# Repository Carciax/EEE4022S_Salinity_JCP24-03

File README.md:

## The Design of a Salinity Sensor for Antarctic Research
**EEE4022S_Salinity_JCP24-03**
 
This project focused on the design of a salinity sensor for measuring the salinity of the sea water beneath the Antarctica ice caps which had a unique habitat and salinity range due to the ice caps expelling large amount of salt through brine channels into the ocean below. The project consisted of two PCB boards, a probe to be inserted through a drilled hole in the ice and a controller to calibrate, request and display measurements. The probe used a complex switching array to measure the average resistance between a pair of either gold or titanium electrodes using a voltage sweep, then it would calculate the waters conductivity, and finally its salinity.

**File Structure**
- EEE4022S 2024 FINAL REPORT CLRCAM007 Clark CF - Pead: The final project report
- CAD: 3D printing files for the pressure sensor waterproof
- Code: The embedded C project code running on the controller and probe boards and the RS485 protocol between them.
- GA Forms: forms required to submit to ECSA
- PCBs: The KiCAD design files for the controller, probe and gold electrode PCBs.
- Presentation: Contains the power point and helper files for the final presentation
- Prototype: The prototype salinity sensor that preceeded this project.
- Report Helper Documents: Documents used for data processing and store from the testing of the probe.
- Report: The LaTeX project file for generating the final report.

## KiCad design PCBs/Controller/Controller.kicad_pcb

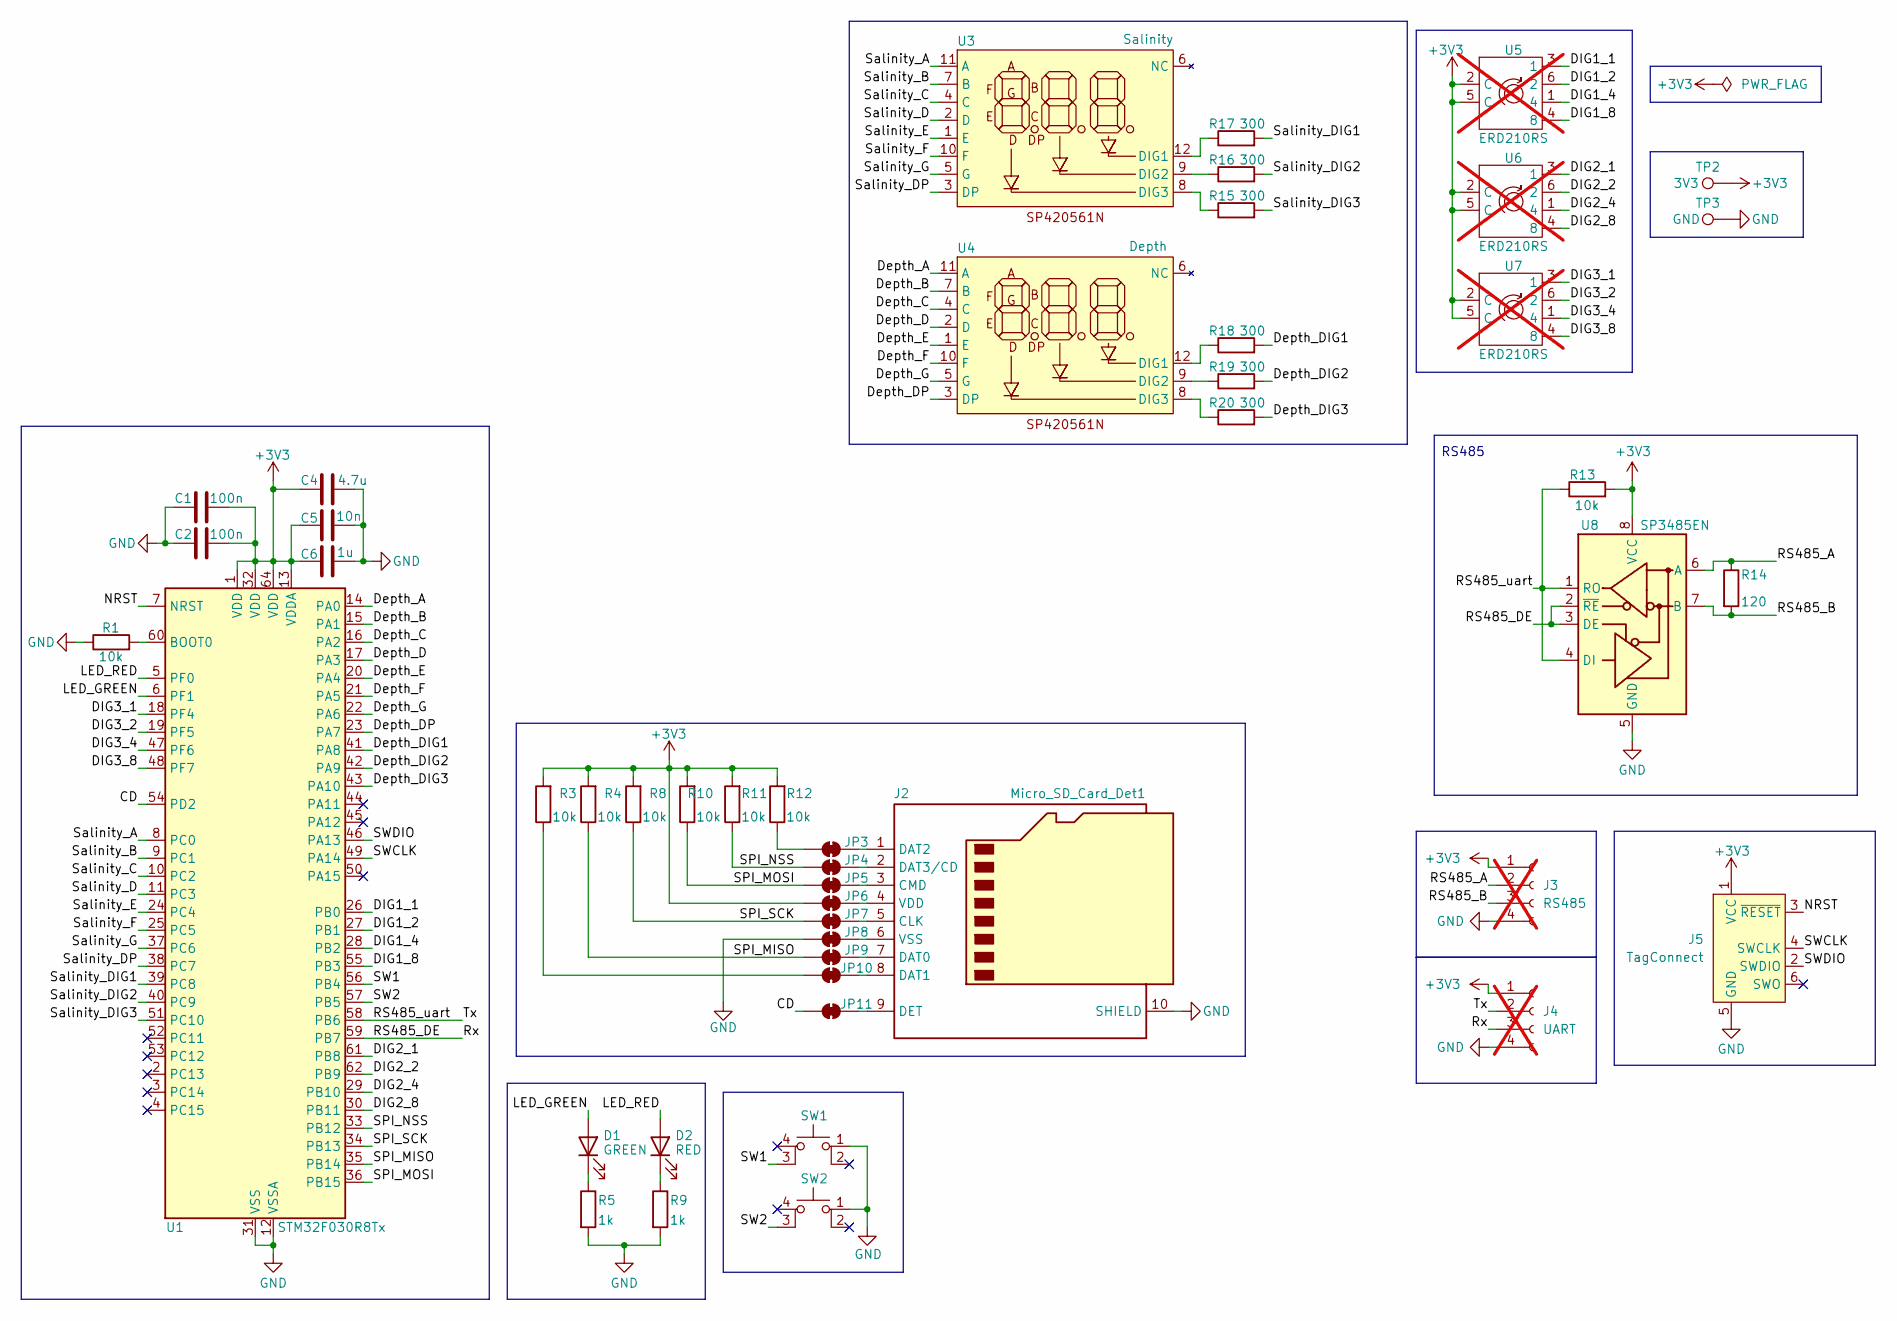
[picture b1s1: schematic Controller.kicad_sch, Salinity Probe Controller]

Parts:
C1, C2: 100n; C_0603_1608Metric; JLC Part no. C14663
C4: 4.7u; C_0603_1608Metric; JLC Part no. C69182
C5: 10n; C_0603_1608Metric; JLC Part no. C57112
C6: 1u; C_0603_1608Metric; JLC Part no. C15849
D1: GREEN; LED_0805_2012Metric; JLC Part no. C2297
D2: RED; LED_0603_1608Metric; JLC Part no. C2286
J2: Micro_SD_Card_Det1; microSDcard; JLC Part no. C393941
J3: RS485; PinHeader_1x04_P2.54mm_Vertical; not fitted
J4: UART; PinHeader_1x04_P2.54mm_Vertical; not fitted
J5: TagConnect; Tag-Connect_TC2030-IDC-NL_2x03_P1.27mm_Vertical
JP3, JP4, JP5, JP6, JP7, JP8, JP9, JP10, JP11: SolderJumper_2_Bridged; SolderJumper-2_P1.3mm_Bridged_Pad1.0x1.5mm
R1, R3, R4, R8, R10, R11, R12, R13: 10k; R_0603_1608Metric; JLC Part no. C25804
R5, R9: 1k; R_0603_1608Metric; JLC Part no. C21190
R14: 120; R_0603_1608Metric; JLC Part no. C22787
R15, R16, R17, R18, R19, R20: 300; R_1206_3216Metric; JLC Part no. C17887
SW1, SW2: Switch; Push_Button_SPDT; JLC Part no. C318884
TP2: 3V3; TestPoint_THTPad_2.0x2.0mm_Drill1.0mm
TP3: GND; TestPoint_THTPad_2.0x2.0mm_Drill1.0mm
U1: STM32F030R8Tx; LQFP-64_10x10mm_P0.5mm; JLC Part no. C39105
U3: Salinity; SP20561; JLC Part no. C98928
U4: Depth; SP20561; JLC Part no. C98928
U5, U6, U7: ERD210RS; ERD2xxxS; not fitted
U8: SP3485EN; SOIC-8_3.9x4.9mm_P1.27mm; JLC Part no. C8963

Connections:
+3V3: C1.2, C2.2, C4.1, C5.2, C6.2, J3.1, J4.1, J5.1 (VCC), JP6.1 (A), R3.2, R4.2, R8.2, R10.2, R11.2, R12.2, R13.2, TP2.1, U1.1 (VDD), U1.13 (VDDA), U1.32 (VDD), U1.64 (VDD), U5.2 (C), U5.5 (C), U6.2 (C), U6.5 (C), U7.2 (C), U7.5 (C), U8.8 (VCC)
/CD: JP11.1 (A), U1.54 (PD2)
/DIG1_1: U1.26 (PB0), U5.3 (1)
/DIG1_2: U1.27 (PB1), U5.6 (2)
/DIG1_4: U1.28 (PB2), U5.1 (4)
/DIG1_8: U1.55 (PB3), U5.4 (8)
/DIG2_1: U1.61 (PB8), U6.3 (1)
/DIG2_2: U1.62 (PB9), U6.6 (2)
/DIG2_4: U1.29 (PB10), U6.1 (4)
/DIG2_8: U1.30 (PB11), U6.4 (8)
/DIG3_1: U1.18 (PF4), U7.3 (1)
/DIG3_2: U1.19 (PF5), U7.6 (2)
/DIG3_4: U1.47 (PF6), U7.1 (4)
/DIG3_8: U1.48 (PF7), U7.4 (8)
/Depth_A: U1.14 (PA0), U4.11 (A)
/Depth_B: U1.15 (PA1), U4.7 (B)
/Depth_C: U1.16 (PA2), U4.4 (C)
/Depth_D: U1.17 (PA3), U4.2 (D)
/Depth_DIG1: R18.2, U1.41 (PA8)
/Depth_DIG2: R19.2, U1.42 (PA9)
/Depth_DIG3: R20.2, U1.43 (PA10)
/Depth_DP: U1.23 (PA7), U4.3 (DP)
/Depth_E: U1.20 (PA4), U4.1 (E)
/Depth_F: U1.21 (PA5), U4.10 (F)
/Depth_G: U1.22 (PA6), U4.5 (G)
/LED_GREEN: D1.2 (A), U1.6 (PF1)
/LED_RED: D2.2 (A), U1.5 (PF0)
/NRST: J5.3 (~RESET), U1.7 (NRST)
/RS485_A: J3.2, R14.1, U8.6 (A)
/RS485_B: J3.3, R14.2, U8.7 (B)
/RS485_DE: J4.3, U1.59 (PB7), U8.2 (~RE), U8.3 (DE)
/RS485_uart: J4.2, R13.1, U1.58 (PB6), U8.1 (RO), U8.4 (DI)
/SPI_MISO: JP9.1 (A), R4.1, U1.35 (PB14)
/SPI_MOSI: JP5.1 (A), R10.1, U1.36 (PB15)
/SPI_NSS: JP4.1 (A), R11.1, U1.33 (PB12)
/SPI_SCK: JP7.1 (A), R8.1, U1.34 (PB13)
/SW1: SW1.3 (K), U1.56 (PB4)
/SW2: SW2.3 (K), U1.57 (PB5)
/SWCLK: J5.4 (SWCLK), U1.49 (PA14)
/SWDIO: J5.2 (SWDIO), U1.46 (PA13)
/Salinity_A: U1.8 (PC0), U3.11 (A)
/Salinity_B: U1.9 (PC1), U3.7 (B)
/Salinity_C: U1.10 (PC2), U3.4 (C)
/Salinity_D: U1.11 (PC3), U3.2 (D)
/Salinity_DIG1: R17.2, U1.39 (PC8)
/Salinity_DIG2: R16.2, U1.40 (PC9)
/Salinity_DIG3: R15.2, U1.51 (PC10)
/Salinity_DP: U1.38 (PC7), U3.3 (DP)
/Salinity_E: U1.24 (PC4), U3.1 (E)
/Salinity_F: U1.25 (PC5), U3.10 (F)
/Salinity_G: U1.37 (PC6), U3.5 (G)
GND: C1.1, C2.1, C4.2, C5.1, C6.1, J2.10 (SHIELD), J3.4, J4.4, J5.5 (GND), JP8.1 (A), R1.1, R5.2, R9.2, SW1.1, SW2.1, TP3.1, U1.12 (VSSA), U1.31 (VSS), U1.63 (VSS), U8.5 (GND)
unnamed: D1.1 (K), R5.1
unnamed: D2.1 (K), R9.1
unnamed: J2.5 (CLK), JP7.2 (B)
unnamed: J2.3 (CMD), JP5.2 (B)
unnamed: J2.7 (DAT0), JP9.2 (B)
unnamed: J2.8 (DAT1), JP10.2 (B)
unnamed: J2.1 (DAT2), JP3.2 (B)
unnamed: J2.2 (DAT3/CD), JP4.2 (B)
unnamed: J2.9 (DET), JP11.2 (B)
unnamed: J2.4 (VDD), JP6.2 (B)
unnamed: J2.6 (VSS), JP8.2 (B)
unnamed: JP3.1 (A), R12.1
unnamed: JP10.1 (A), R3.1
unnamed: R1.2, U1.60 (BOOT0)
unnamed: R17.1, U3.12 (DIG1)
unnamed: R16.1, U3.9 (DIG2)
unnamed: R15.1, U3.8 (DIG3)
unnamed: R18.1, U4.12 (DIG1)
unnamed: R19.1, U4.9 (DIG2)
unnamed: R20.1, U4.8 (DIG3)

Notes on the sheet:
RS485

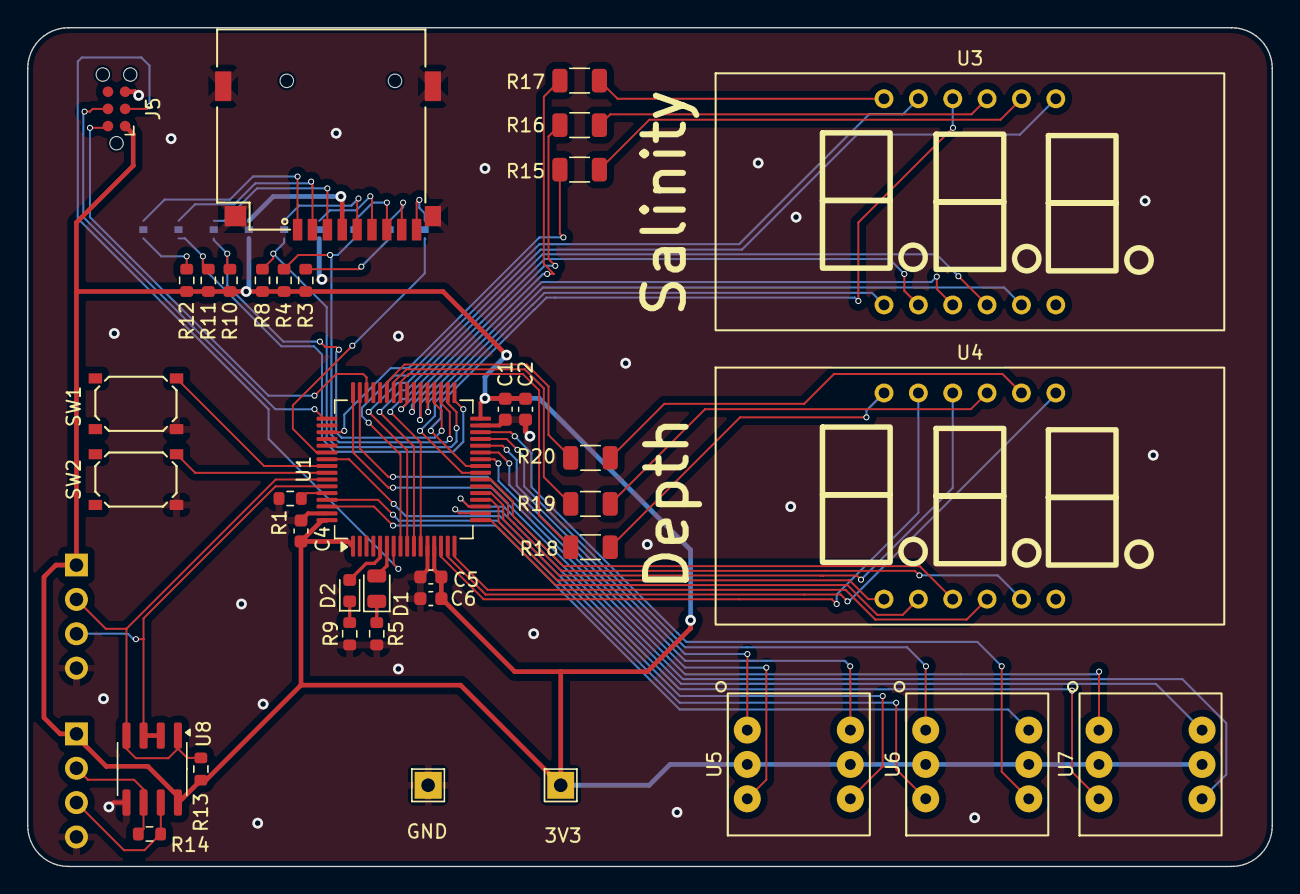
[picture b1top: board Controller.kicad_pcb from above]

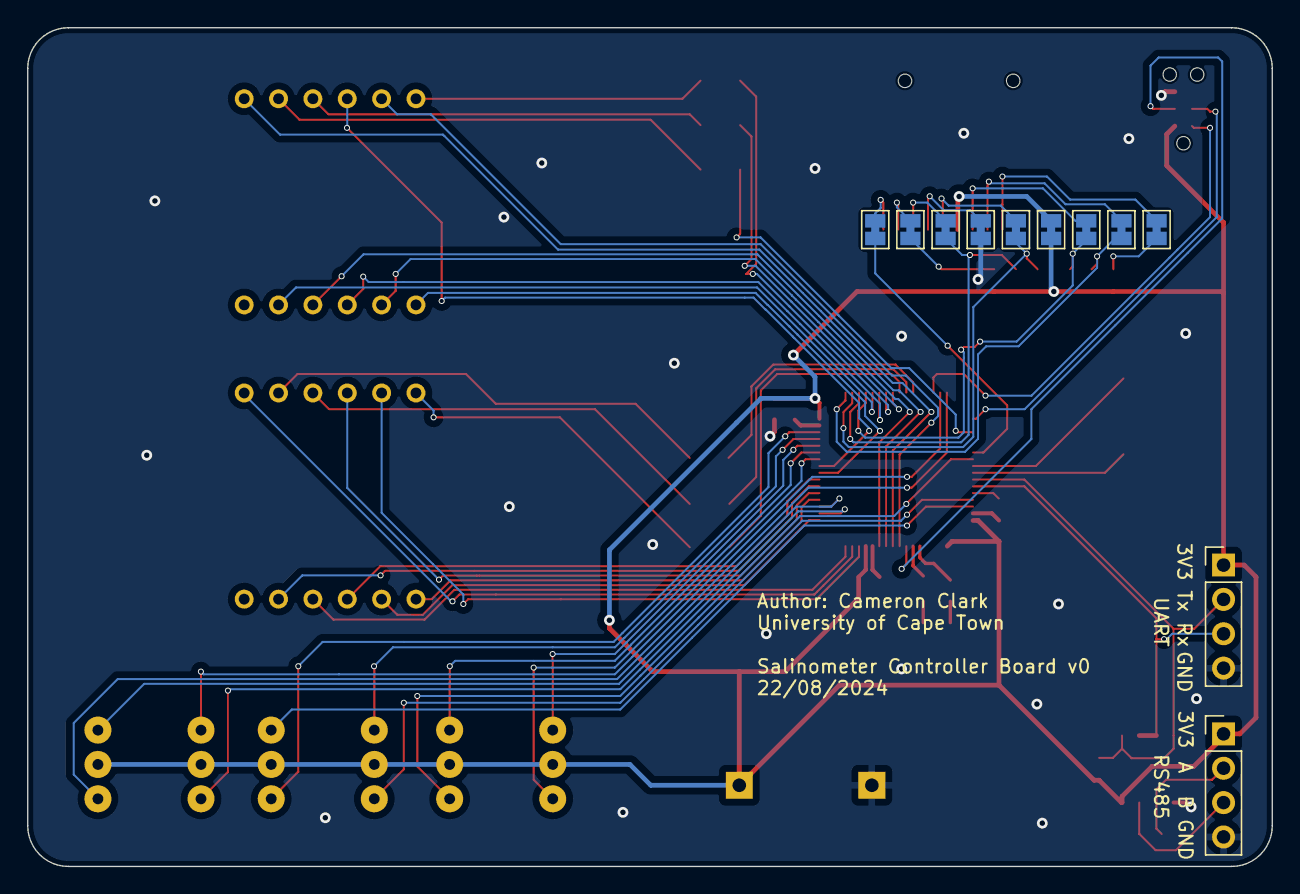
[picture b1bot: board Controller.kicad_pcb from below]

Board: 2 copper layers, 92.0 x 62.0 mm, 48 parts (11 on the bottom side), 72 nets.

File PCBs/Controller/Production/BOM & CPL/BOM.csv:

"Reference";"Value";"Datasheet";"Footprint";"Qty";"JLC Part no.";"Extended";"Cost"
"C1";"100n";"~";"Capacitor_SMD:C_0603_1608Metric";"1";"C14663";"False";"0,0021"
"C2";"100n";"~";"Capacitor_SMD:C_0603_1608Metric";"1";"C14663";"False";"0,0021"
"C4";"4.7u";"~";"Capacitor_SMD:C_0603_1608Metric";"1";"C69182";"False";"0,0055"
"C5";"10n";"~";"Capacitor_SMD:C_0603_1608Metric";"1";"C57112";"False";"0,0023"
"C6";"1u";"~";"Capacitor_SMD:C_0603_1608Metric";"1";"C15849";"False";"0,0043"
"D1";"GREEN";"~";"LED_SMD:LED_0805_2012Metric";"1";"C2297";"False";"0,0095"
"D2";"RED";"~";"LED_SMD:LED_0603_1608Metric";"1";"C2286";"False";"0,0053"
"J2";"Micro_SD_Card_Det1";"https://datasheet.lcsc.com/lcsc/2110151630_XKB-Connectivity-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";"4022S:microSDcard";"1";"C393941";"True";"0,0443"
"J3";"RS485";"~";"Connector_PinHeader_2.54mm:PinHeader_1x04_P2.54mm_Vertical";"1";"";"";""
"J4";"UART";"~";"Connector_PinHeader_2.54mm:PinHeader_1x04_P2.54mm_Vertical";"1";"";"";""
"R1";"10k";"~";"Resistor_SMD:R_0603_1608Metric";"1";"C25804";"False";"0,0008"
"R3";"10k";"~";"Resistor_SMD:R_0603_1608Metric";"1";"C25804";"False";"0,0008"
"R4";"10k";"~";"Resistor_SMD:R_0603_1608Metric";"1";"C25804";"False";"0,0008"
"R5";"1k";"~";"Resistor_SMD:R_0603_1608Metric";"1";"C21190";"False";"0,0009"
"R8";"10k";"~";"Resistor_SMD:R_0603_1608Metric";"1";"C25804";"False";"0,0008"
"R9";"1k";"~";"Resistor_SMD:R_0603_1608Metric";"1";"C21190";"False";"0,0009"
"R10";"10k";"~";"Resistor_SMD:R_0603_1608Metric";"1";"C25804";"False";"0,0008"
"R11";"10k";"~";"Resistor_SMD:R_0603_1608Metric";"1";"C25804";"False";"0,0008"
"R12";"10k";"~";"Resistor_SMD:R_0603_1608Metric";"1";"C25804";"False";"0,0008"
"R13";"10k";"~";"Resistor_SMD:R_0603_1608Metric";"1";"C25804";"False";"0,0008"
"R14";"120";"~";"Resistor_SMD:R_0603_1608Metric";"1";"C22787";"False";"0,0010"
"R15";"300";"~";"Resistor_SMD:R_1206_3216Metric";"1";"C17887";"False";"0,0028"
"R16";"300";"~";"Resistor_SMD:R_1206_3216Metric";"1";"C17887";"False";"0,0028"
"R17";"300";"~";"Resistor_SMD:R_1206_3216Metric";"1";"C17887";"False";"0,0028"
"R18";"300";"~";"Resistor_SMD:R_1206_3216Metric";"1";"C17887";"False";"0,0028"
"R19";"300";"~";"Resistor_SMD:R_1206_3216Metric";"1";"C17887";"False";"0,0028"
"R20";"300";"~";"Resistor_SMD:R_1206_3216Metric";"1";"C17887";"False";"0,0028"
"SW1";"Switch";"http://www.apem.com/int/index.php?controller=attachment&id_a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";"4022S:Push_Button_SPDT";"1";"C318884";"False";"0,0143"
"SW2";"Switch";"http://www.apem.com/int/index.php?controller=attachment&id_a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";"4022S:Push_Button_SPDT";"1";"C318884";"False";"0,0143"
"TP2";"3V3";"~";"TestPoint:TestPoint_THTPad_2.0x2.0mm_Drill1.0mm";"1";"";"";""
"TP3";"GND";"~";"TestPoint:TestPoint_THTPad_2.0x2.0mm_Drill1.0mm";"1";"";"";""
"U1";"STM32F030R8Tx";"https://www.st.com/resource/en/datasheet/stm32f030r8.pdf";"Package_QFP:LQFP-64_10x10mm_P0.5mm";"1";"C39105";"True";"0,7545"
"U3";"Salinity";"";"4022S:SP20561";"1";"C98928";"True";"0,4110"
"U4";"Depth";"";"4022S:SP20561";"1";"C98928";"True";"0,4110"
"U5";"ERD210RS";"";"4022S:ERD2xxxS";"1";"";"";""
"U6";"ERD210RS";"";"4022S:ERD2xxxS";"1";"";"";""
"U7";"ERD210RS";"";"4022S:ERD2xxxS";"1";"";"";""
"U8";"SP3485EN";"http://www.icbase.com/pdf/SPX/SPX00480106.pdf";"Package_SO:SOIC-8_3.9x4.9mm_P1.27mm";"1";"C8963";"False";"0,3076"

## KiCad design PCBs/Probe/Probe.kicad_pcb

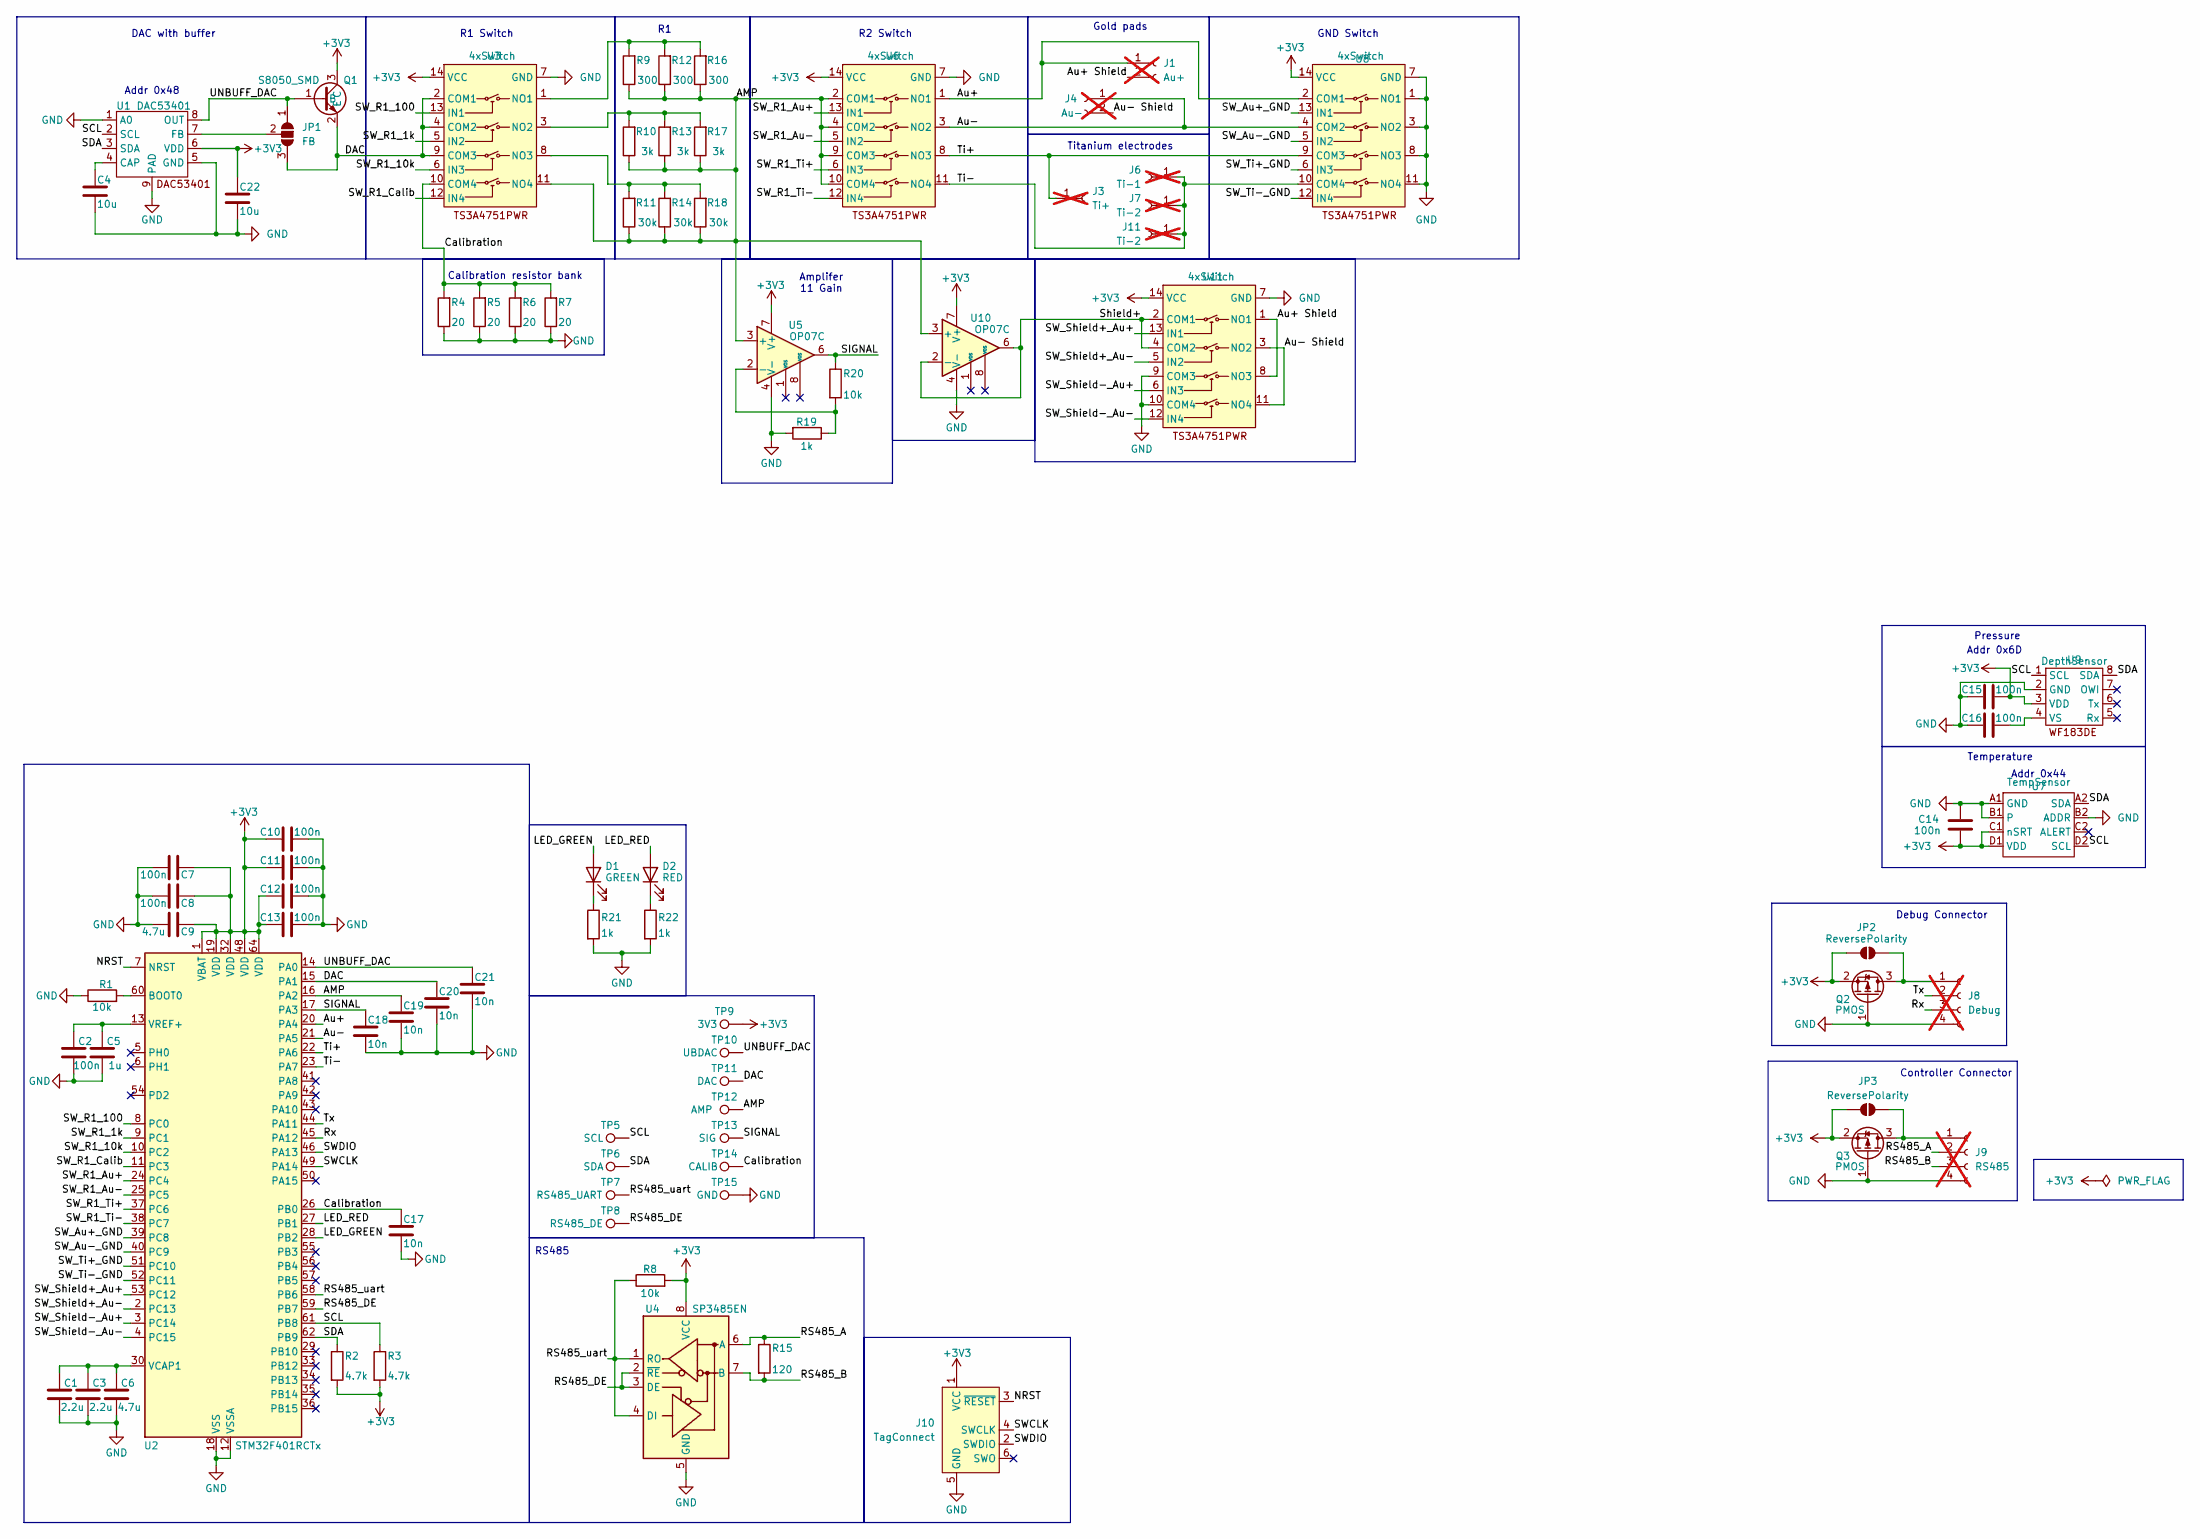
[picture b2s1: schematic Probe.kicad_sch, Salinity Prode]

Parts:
C1, C3: 2.2u; C_0603_1608Metric; JLC Part no. C23630
C2, C7, C8, C10, C11, C12, C13, C14, C15, C16: 100n; C_0603_1608Metric; JLC Part no. C14663
C4, C22: 10u; C_0603_1608Metric; JLC Part no. C19702
C5: 1u; C_0603_1608Metric; JLC Part no. C15849
C6, C9: 4.7u; C_0603_1608Metric; JLC Part no. C69182
C17, C18, C19, C20, C21: 10n; C_0402_1005Metric; JLC Part no. C15195
D1: GREEN; LED_0805_2012Metric; JLC Part no. C2297
D2: RED; LED_0603_1608Metric; JLC Part no. C2286
J1: Au+; Au_Electrode; not fitted
J3: Ti+; PinHeader_1x01_P2.54mm_Vertical; not fitted
J4: Au-; Au_Electrode; not fitted
J6: Ti-1; PinHeader_1x01_P2.54mm_Vertical; not fitted
J7, J11: Ti-2; PinHeader_1x01_P2.54mm_Vertical; not fitted
J8: Debug; PinSocket_1x04_P2.54mm_Vertical; not fitted
J9: RS485; PinSocket_1x04_P2.54mm_Vertical; not fitted
J10: TagConnect; Tag-Connect_TC2030-IDC-NL_2x03_P1.27mm_Vertical
JP1: FB; SolderJumper-3_P2.0mm_Open_TrianglePad1.0x1.5mm
JP2, JP3: ReversePolarity; SolderJumper-2_P1.3mm_Open_TrianglePad1.0x1.5mm
Q1: S8050_SMD; SOT-23-3; JLC Part no. C2146
Q2, Q3: PMOS; SOT-23; JLC Part no. C15127
R1, R8: 10k; R_0603_1608Metric; JLC Part no. C25804
R2, R3: 4.7k; R_0603_1608Metric; JLC Part no. C23162
R4, R5, R6, R7: 20; R_0603_1608Metric; JLC Part no. C22950
R9, R12, R16: 300; R_0603_1608Metric; JLC Part no. C23025
R10, R13, R17: 3k; R_0603_1608Metric; JLC Part no. C4211
R11, R14, R18: 30k; R_0603_1608Metric; JLC Part no. C22984
R15: 120; R_0603_1608Metric; JLC Part no. C22787
R19: 1k; R_1206_3216Metric; JLC Part no. C4410
R20: 10k; R_1206_3216Metric; JLC Part no. C17902
R21, R22: 1k; R_0603_1608Metric; JLC Part no. C21190
TP5: SCL; TestPoint_THTPad_2.0x2.0mm_Drill1.0mm
TP6: SDA; TestPoint_THTPad_2.0x2.0mm_Drill1.0mm
TP7: RS485_UART; TestPoint_THTPad_2.0x2.0mm_Drill1.0mm
TP8: RS485_DE; TestPoint_THTPad_2.0x2.0mm_Drill1.0mm
TP9: 3V3; TestPoint_THTPad_2.0x2.0mm_Drill1.0mm
TP10: UBDAC; TestPoint_THTPad_2.0x2.0mm_Drill1.0mm
TP11: DAC; TestPoint_THTPad_2.0x2.0mm_Drill1.0mm
TP12: AMP; TestPoint_THTPad_2.0x2.0mm_Drill1.0mm
TP13: SIG; TestPoint_THTPad_2.0x2.0mm_Drill1.0mm
TP14: CALIB; TestPoint_THTPad_2.0x2.0mm_Drill1.0mm
TP15: GND; TestPoint_THTPad_2.0x2.0mm_Drill1.0mm
U1: DAC53401; WSON-8-1EP_2x2mm_P0.5mm_EP0.9x1.6mm; JLC Part no. C2861165
U2: STM32F401RCTx; LQFP-64_10x10mm_P0.5mm; JLC Part no. C1339473
U3, U6, U8, U11: 4xSwitch; TSSOP-14_4.4x5mm_P0.65mm; JLC Part no. C128399
U4: SP3485EN; SOIC-8_3.9x4.9mm_P1.27mm; JLC Part no. C8963
U5, U10: OP07C; SOIC-8_3.9x4.9mm_P1.27mm; JLC Part no. C7433
U7: TempSensor; WLCSP-8_1.551x2.284mm_P0.5mm; JLC Part no. C2758003
U9: DepthSensor; WF183DE; JLC Part no. C20415992

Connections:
+3V3: C7.1, C8.1, C9.1, C10.1, C11.1, C12.1, C13.1, C14.2, C15.2, C22.1, J10.1 (VCC), JP2.1 (A), JP3.1 (A), Q1.3 (C), Q2.2 (S), Q3.2 (S), R2.2, R3.2, R8.2, TP9.1, U1.6 (VDD), U2.1 (VBAT), U2.19 (VDD), U2.32 (VDD), U2.48 (VDD), U2.64 (VDD), U3.14 (VCC), U4.8 (VCC), U5.7 (V+), U6.14 (VCC), U7.C1 (nSRT), U7.D1 (VDD), U8.14 (VCC), U9.3 (VDD), U10.7 (V+), U11.14 (VCC)
/AMP: C19.1, R9.1, R10.1, R11.1, R12.1, R13.1, R14.1, R16.1, R17.1, R18.1, TP12.1, U2.16 (PA2), U3.11 (NO4), U5.3 (+), U6.2 (COM1), U6.4 (COM2), U6.9 (COM3), U6.10 (COM4), U10.3 (+)
/Au+: J1.1, U2.20 (PA4), U6.1 (NO1), U8.2 (COM1)
/Au+ Shield: J1.2, U11.1 (NO1), U11.8 (NO3)
/Au-: J4.1, U2.21 (PA5), U6.3 (NO2), U8.4 (COM2)
/Au- Shield: J4.2, U11.3 (NO2), U11.11 (NO4)
/Calibration: C17.1, R4.2, R5.2, R6.2, R7.2, TP14.1, U2.26 (PB0), U3.10 (COM4)
/DAC: C20.1, JP1.3 (B), Q1.2 (E), TP11.1, U2.15 (PA1), U3.2 (COM1), U3.4 (COM2), U3.9 (COM3)
/LED_GREEN: D1.2 (A), U2.28 (PB2)
/LED_RED: D2.2 (A), U2.27 (PB1)
/NRST: J10.3 (~RESET), U2.7 (NRST)
/RS485_A: J9.2, R15.1, U4.6 (A)
/RS485_B: J9.3, R15.2, U4.7 (B)
/RS485_DE: TP8.1, U2.59 (PB7), U4.2 (~RE), U4.3 (DE)
/RS485_uart: R8.1, TP7.1, U2.58 (PB6), U4.1 (RO), U4.4 (DI)
/Rx: J8.3, U2.45 (PA12)
/SCL: R3.1, TP5.1, U1.2 (SCL), U2.61 (PB8), U7.D2 (SCL), U9.1 (SCL)
/SDA: R2.1, TP6.1, U1.3 (SDA), U2.62 (PB9), U7.A2 (SDA), U9.8 (SDA)
/SIGNAL: C18.1, R20.1, TP13.1, U2.17 (PA3), U5.6
/SWCLK: J10.4 (SWCLK), U2.49 (PA14)
/SWDIO: J10.2 (SWDIO), U2.46 (PA13)
/SW_Au+_GND: U2.39 (PC8), U8.13 (IN1)
/SW_Au-_GND: U2.40 (PC9), U8.5 (IN2)
/SW_R1_1k: U2.9 (PC1), U3.5 (IN2)
/SW_R1_10k: U2.10 (PC2), U3.6 (IN3)
/SW_R1_100: U2.8 (PC0), U3.13 (IN1)
/SW_R1_Au+: U2.24 (PC4), U6.13 (IN1)
/SW_R1_Au-: U2.25 (PC5), U6.5 (IN2)
/SW_R1_Calib: U2.11 (PC3), U3.12 (IN4)
/SW_R1_Ti+: U2.37 (PC6), U6.6 (IN3)
/SW_R1_Ti-: U2.38 (PC7), U6.12 (IN4)
/SW_Shield+_Au+: U2.53 (PC12), U11.13 (IN1)
/SW_Shield+_Au-: U2.2 (PC13), U11.5 (IN2)
/SW_Shield-_Au+: U2.3 (PC14), U11.6 (IN3)
/SW_Shield-_Au-: U2.4 (PC15), U11.12 (IN4)
/SW_Ti+_GND: U2.51 (PC10), U8.6 (IN3)
/SW_Ti-_GND: U2.52 (PC11), U8.12 (IN4)
/Shield+: U10.2 (-), U10.6, U11.2 (COM1), U11.4 (COM2)
/Ti+: J3.1, U2.22 (PA6), U6.8 (NO3), U8.9 (COM3)
/Ti-: J6.1, J7.1, J11.1, U2.23 (PA7), U6.11 (NO4), U8.10 (COM4)
/Tx: J8.2, U2.44 (PA11)
/UNBUFF_DAC: C21.1, JP1.1 (A), Q1.1 (B), TP10.1, U1.8 (OUT), U2.14 (PA0)
GND: C1.1, C2.1, C3.1, C4.2, C5.1, C6.1, C7.2, C8.2, C9.2, C10.2, C11.2, C12.2, C13.2, C14.1, C15.1, C16.1, C17.2, C18.2, C19.2, C20.2, C21.2, C22.2, J8.4, J9.4, J10.5 (GND), Q2.1 (G), Q3.1 (G), R1.1, R4.1, R5.1, R6.1, R7.1, R19.2, R21.2, R22.2, TP15.1, U1.1 (A0), U1.5 (GND), U1.9 (PAD), U2.12 (VSSA), U2.18 (VSS), U2.31 (VSS), U2.47 (VSS), U2.63 (VSS), U3.7 (GND), U4.5 (GND), U5.4 (V-), U6.7 (GND), U7.A1 (GND), U7.B1, U7.B2 (ADDR), U8.1 (NO1), U8.3 (NO2), U8.7 (GND), U8.8 (NO3), U8.11 (NO4), U9.2 (GND), U10.4 (V-), U11.7 (GND), U11.9 (COM3), U11.10 (COM4)
unnamed: D1.1 (K), R21.1
unnamed: D2.1 (K), R22.1
unnamed: J8.1, JP2.2 (B), Q2.3 (D)
unnamed: J9.1, JP3.2 (B), Q3.3 (D)
unnamed: JP1.2 (C), U1.7 (FB)
unnamed: C4.1, U1.4 (CAP)
unnamed: R1.2, U2.60 (BOOT0)
unnamed: C1.2, C3.2, C6.2, U2.30 (VCAP1)
unnamed: C2.2, C5.2, U2.13 (VREF+)
unnamed: R9.2, R12.2, R16.2, U3.1 (NO1)
unnamed: R10.2, R13.2, R17.2, U3.3 (NO2)
unnamed: R11.2, R14.2, R18.2, U3.8 (NO3)
unnamed: R19.1, R20.2, U5.2 (-)
unnamed: C16.2, U9.4 (VS)

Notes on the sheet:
R1 Switch
Gold pads
GND Switch
Debug Connector
Pressure
Addr 0x48
RS485
DAC with buffer
Addr 0x44
Calibration resistor bank
Controller Connector
Titanium electrodes
R2 Switch
Amplifer 11 Gain
Addr 0x6D
Temperature

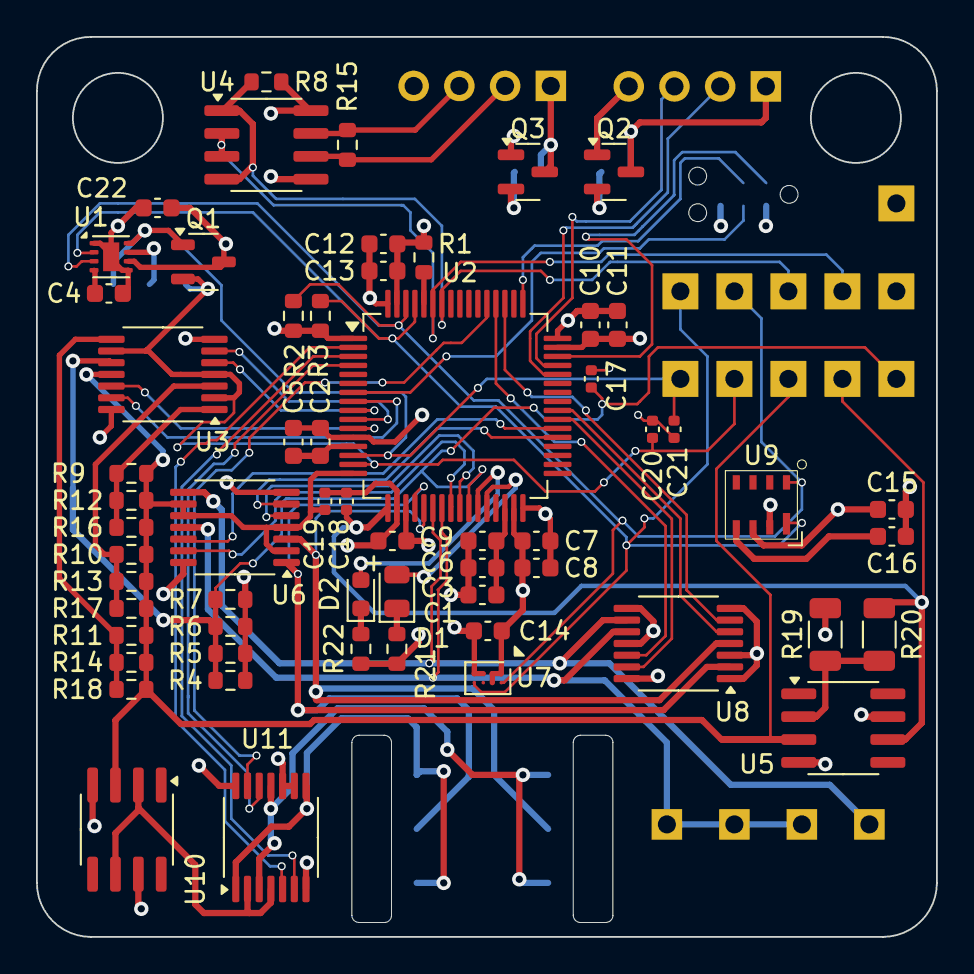
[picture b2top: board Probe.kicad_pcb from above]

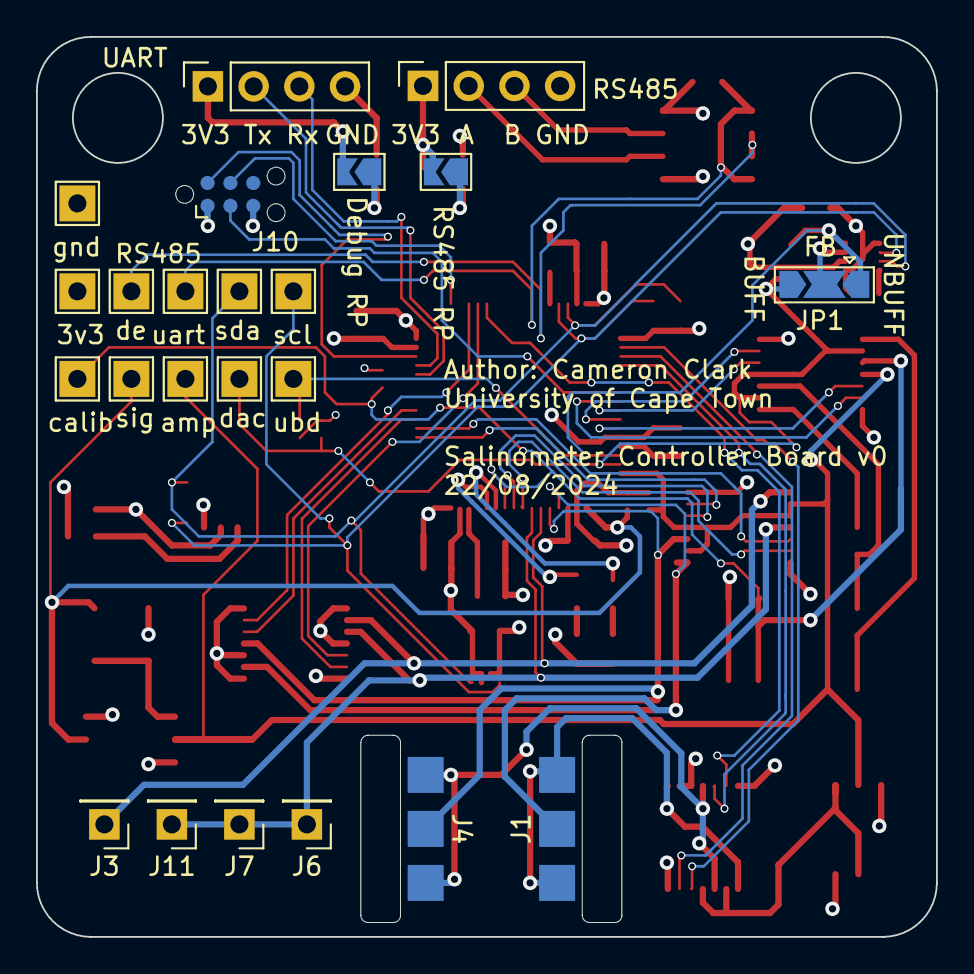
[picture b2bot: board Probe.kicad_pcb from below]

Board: 4 copper layers, 50.0 x 50.0 mm, 83 parts (23 on the bottom side), 57 nets.

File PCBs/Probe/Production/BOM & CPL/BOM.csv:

"Reference";"Value";"Datasheet";"Footprint";"Qty";"JLC Part no.";"Extended";"Cost"
"C1";"2.2u";"~";"Capacitor_SMD:C_0603_1608Metric";"1";"C23630";"False";"0,0055"
"C2";"100n";"~";"Capacitor_SMD:C_0603_1608Metric";"1";"C14663";"False";"0,0021"
"C3";"2.2u";"~";"Capacitor_SMD:C_0603_1608Metric";"1";"C23630";"False";"0,0055"
"C4";"10u";"~";"Capacitor_SMD:C_0603_1608Metric";"1";"C19702";"False";"0,0048"
"C5";"1u";"~";"Capacitor_SMD:C_0603_1608Metric";"1";"C15849";"False";"0,0043"
"C6";"4.7u";"~";"Capacitor_SMD:C_0603_1608Metric";"1";"C69182";"False";"0,0055"
"C7";"100n";"~";"Capacitor_SMD:C_0603_1608Metric";"1";"C14663";"False";"0,0021"
"C8";"100n";"~";"Capacitor_SMD:C_0603_1608Metric";"1";"C14663";"False";"0,0021"
"C9";"4.7u";"~";"Capacitor_SMD:C_0603_1608Metric";"1";"C69182";"False";"0,0055"
"C10";"100n";"~";"Capacitor_SMD:C_0603_1608Metric";"1";"C14663";"False";"0,0021"
"C11";"100n";"~";"Capacitor_SMD:C_0603_1608Metric";"1";"C14663";"False";"0,0021"
"C12";"100n";"~";"Capacitor_SMD:C_0603_1608Metric";"1";"C14663";"False";"0,0021"
"C13";"100n";"~";"Capacitor_SMD:C_0603_1608Metric";"1";"C14663";"False";"0,0021"
"C14";"100n";"~";"Capacitor_SMD:C_0603_1608Metric";"1";"C14663";"False";"0,0021"
"C15";"100n";"~";"Capacitor_SMD:C_0603_1608Metric";"1";"C14663";"False";"0,0021"
"C16";"100n";"~";"Capacitor_SMD:C_0603_1608Metric";"1";"C14663";"False";"0,0021"
"C17";"10n";"~";"Capacitor_SMD:C_0402_1005Metric";"1";"C15195";"False";"0,0012"
"C18";"10n";"~";"Capacitor_SMD:C_0402_1005Metric";"1";"C15195";"False";"0,0012"
"C19";"10n";"~";"Capacitor_SMD:C_0402_1005Metric";"1";"C15195";"False";"0,0012"
"C20";"10n";"~";"Capacitor_SMD:C_0402_1005Metric";"1";"C15195";"False";"0,0012"
"C21";"10n";"~";"Capacitor_SMD:C_0402_1005Metric";"1";"C15195";"False";"0,0012"
"C22";"10u";"~";"Capacitor_SMD:C_0603_1608Metric";"1";"C19702";"False";"0,0048"
"D1";"GREEN";"~";"LED_SMD:LED_0805_2012Metric";"1";"C2297";"False";"0,0095"
"D2";"RED";"~";"LED_SMD:LED_0603_1608Metric";"1";"C2286";"False";"0,0053"
"J1";"Au+";"~";"4022S:Au_Electrode";"1";"";"";""
"J3";"Ti+";"~";"Connector_PinHeader_2.54mm:PinHeader_1x01_P2.54mm_Vertical";"1";"";"";""
"J4";"Au-";"~";"4022S:Au_Electrode";"1";"";"";""
"J6";"Ti-1";"~";"Connector_PinHeader_2.54mm:PinHeader_1x01_P2.54mm_Vertical";"1";"";"";""
"J7";"Ti-2";"~";"Connector_PinHeader_2.54mm:PinHeader_1x01_P2.54mm_Vertical";"1";"";"";""
"J8";"Debug";"~";"Connector_PinSocket_2.54mm:PinSocket_1x04_P2.54mm_Vertical";"1";"";"";""
"J9";"RS485";"~";"Connector_PinSocket_2.54mm:PinSocket_1x04_P2.54mm_Vertical";"1";"";"";""
"J11";"Ti-2";"~";"Connector_PinHeader_2.54mm:PinHeader_1x01_P2.54mm_Vertical";"1";"";"";""
"Q1";"S8050_SMD";"";"Package_TO_SOT_SMD:SOT-23-3";"1";"C2146";"False";"0,0131"
"Q2";"PMOS";"http://www.aosmd.com/pdfs/datasheet/AO3401A.pdf";"Package_TO_SOT_SMD:SOT-23";"1";"C15127";"False";"0,0387"
"Q3";"PMOS";"http://www.aosmd.com/pdfs/datasheet/AO3401A.pdf";"Package_TO_SOT_SMD:SOT-23";"1";"C15127";"False";"0,0387"
"R1";"10k";"~";"Resistor_SMD:R_0603_1608Metric";"1";"C25804";"False";"0,0008"
"R2";"4.7k";"~";"Resistor_SMD:R_0603_1608Metric";"1";"C23162";"False";"0,0010"
"R3";"4.7k";"~";"Resistor_SMD:R_0603_1608Metric";"1";"C23162";"False";"0,0010"
"R4";"20";"~";"Resistor_SMD:R_0603_1608Metric";"1";"C22950";"False";"0,0009"
"R5";"20";"~";"Resistor_SMD:R_0603_1608Metric";"1";"C22950";"False";"0,0009"
"R6";"20";"~";"Resistor_SMD:R_0603_1608Metric";"1";"C22950";"False";"0,0009"
"R7";"20";"~";"Resistor_SMD:R_0603_1608Metric";"1";"C22950";"False";"0,0009"
"R8";"10k";"~";"Resistor_SMD:R_0603_1608Metric";"1";"C25804";"False";"0,0008"
"R9";"300";"~";"Resistor_SMD:R_0603_1608Metric";"1";"C23025";"False";"0,0010"
"R10";"3k";"~";"Resistor_SMD:R_0603_1608Metric";"1";"C4211";"False";"0,0009"
"R11";"30k";"~";"Resistor_SMD:R_0603_1608Metric";"1";"C22984";"False";"0,0009"
"R12";"300";"~";"Resistor_SMD:R_0603_1608Metric";"1";"C23025";"False";"0,0010"
"R13";"3k";"~";"Resistor_SMD:R_0603_1608Metric";"1";"C4211";"False";"0,0009"
"R14";"30k";"~";"Resistor_SMD:R_0603_1608Metric";"1";"C22984";"False";"0,0009"
"R15";"120";"~";"Resistor_SMD:R_0603_1608Metric";"1";"C22787";"False";"0,0010"
"R16";"300";"~";"Resistor_SMD:R_0603_1608Metric";"1";"C23025";"False";"0,0010"
"R17";"3k";"~";"Resistor_SMD:R_0603_1608Metric";"1";"C4211";"False";"0,0009"
"R18";"30k";"~";"Resistor_SMD:R_0603_1608Metric";"1";"C22984";"False";"0,0009"
"R19";"1k";"~";"Resistor_SMD:R_1206_3216Metric";"1";"C4410";"False";"0,0027"
"R20";"10k";"~";"Resistor_SMD:R_1206_3216Metric";"1";"C17902";"False";"0,0028"
"R21";"1k";"~";"Resistor_SMD:R_0603_1608Metric";"1";"C21190";"False";"0,0009"
"R22";"1k";"~";"Resistor_SMD:R_0603_1608Metric";"1";"C21190";"False";"0,0009"
"TP5";"SCL";"~";"TestPoint:TestPoint_THTPad_2.0x2.0mm_Drill1.0mm";"1";"";"";""
"TP6";"SDA";"~";"TestPoint:TestPoint_THTPad_2.0x2.0mm_Drill1.0mm";"1";"";"";""
"TP7";"RS485_UART";"~";"TestPoint:TestPoint_THTPad_2.0x2.0mm_Drill1.0mm";"1";"";"";""
"TP8";"RS485_DE";"~";"TestPoint:TestPoint_THTPad_2.0x2.0mm_Drill1.0mm";"1";"";"";""
"TP9";"3V3";"~";"TestPoint:TestPoint_THTPad_2.0x2.0mm_Drill1.0mm";"1";"";"";""
"TP10";"UBDAC";"~";"TestPoint:TestPoint_THTPad_2.0x2.0mm_Drill1.0mm";"1";"";"";""
"TP11";"DAC";"~";"TestPoint:TestPoint_THTPad_2.0x2.0mm_Drill1.0mm";"1";"";"";""
"TP12";"AMP";"~";"TestPoint:TestPoint_THTPad_2.0x2.0mm_Drill1.0mm";"1";"";"";""
"TP13";"SIG";"~";"TestPoint:TestPoint_THTPad_2.0x2.0mm_Drill1.0mm";"1";"";"";""
"TP14";"CALIB";"~";"TestPoint:TestPoint_THTPad_2.0x2.0mm_Drill1.0mm";"1";"";"";""
"TP15";"GND";"~";"TestPoint:TestPoint_THTPad_2.0x2.0mm_Drill1.0mm";"1";"";"";""
"U1";"DAC53401";"";"Package_SON:WSON-8-1EP_2x2mm_P0.5mm_EP0.9x1.6mm";"1";"C2861165";"True";"0,6660"
"U2";"STM32F401RCTx";"https://www.st.com/resource/en/datasheet/stm32f401rc.pdf";"Package_QFP:LQFP-64_10x10mm_P0.5mm";"1";"C1339473";"True";"2,1735"
"U3";"4xSwitch";"";"Package_SO:TSSOP-14_4.4x5mm_P0.65mm";"1";"C128399";"True";"1,4775"
"U4";"SP3485EN";"http://www.icbase.com/pdf/SPX/SPX00480106.pdf";"Package_SO:SOIC-8_3.9x4.9mm_P1.27mm";"1";"C8963";"False";"0,3076"
"U5";"OP07C";"https://www.analog.com/media/en/technical-documentation/data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";"Package_SO:SOIC-8_3.9x4.9mm_P1.27mm";"1";"C7433";"False";"0,1247"
"U6";"4xSwitch";"";"Package_SO:TSSOP-14_4.4x5mm_P0.65mm";"1";"C128399";"True";"1,4775"
"U7";"TempSensor";"";"Package_CSP:WLCSP-8_1.551x2.284mm_P0.5mm";"1";"C2758003";"True";"0,5325"
"U8";"4xSwitch";"";"Package_SO:TSSOP-14_4.4x5mm_P0.65mm";"1";"C128399";"True";"1,4775"
"U9";"DepthSensor";"";"4022S:WF183DE";"1";"C20415992";"True";"0,6315"
"U10";"OP07C";"https://www.analog.com/media/en/technical-documentation/data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";"Package_SO:SOIC-8_3.9x4.9mm_P1.27mm";"1";"C7433";"False";"0,1247"
"U11";"4xSwitch";"";"Package_SO:TSSOP-14_4.4x5mm_P0.65mm";"1";"C128399";"True";"1,4775"

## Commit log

2024-07-27 added report template
2024-08-10 started pcbs
2024-08-19 pcb work
2024-08-28 kicad changes
2024-09-10 heading for lit review
2024-09-16 salinity-conductivity eqn
2024-09-16 salinity conductivity eqn
2024-09-22 report writing
2024-09-27 controller test code
2024-10-01 resisitivity and salinity library
2024-10-02 temp and depth sensor
2024-10-03 readable code uart
2024-10-05 board to board coms work
2024-10-08 testing phase 1 started
2024-10-10 testing phase 1 complete
2024-10-15 prepping for salt water tests
2024-10-17 more tests
2024-10-20 grammarly intro-theory
2024-10-22 design and implementation grammarly
2024-10-22 implementation grammarly
2024-10-23 testing complete
2024-10-23 last graphs
2024-10-24 finishing touches
2024-10-24 final submission
2024-10-30 final commit
2024-10-30 final final commit
2024-10-30 small commit
2024-10-30 final commits
2025-10-22 last commit
2025-10-22 Refine README formatting and file structure details
    Updated header formatting and improved file structure section.
